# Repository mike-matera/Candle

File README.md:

Candle
======

This is the PCB designed for my candle controller. It's done using Eagle light.

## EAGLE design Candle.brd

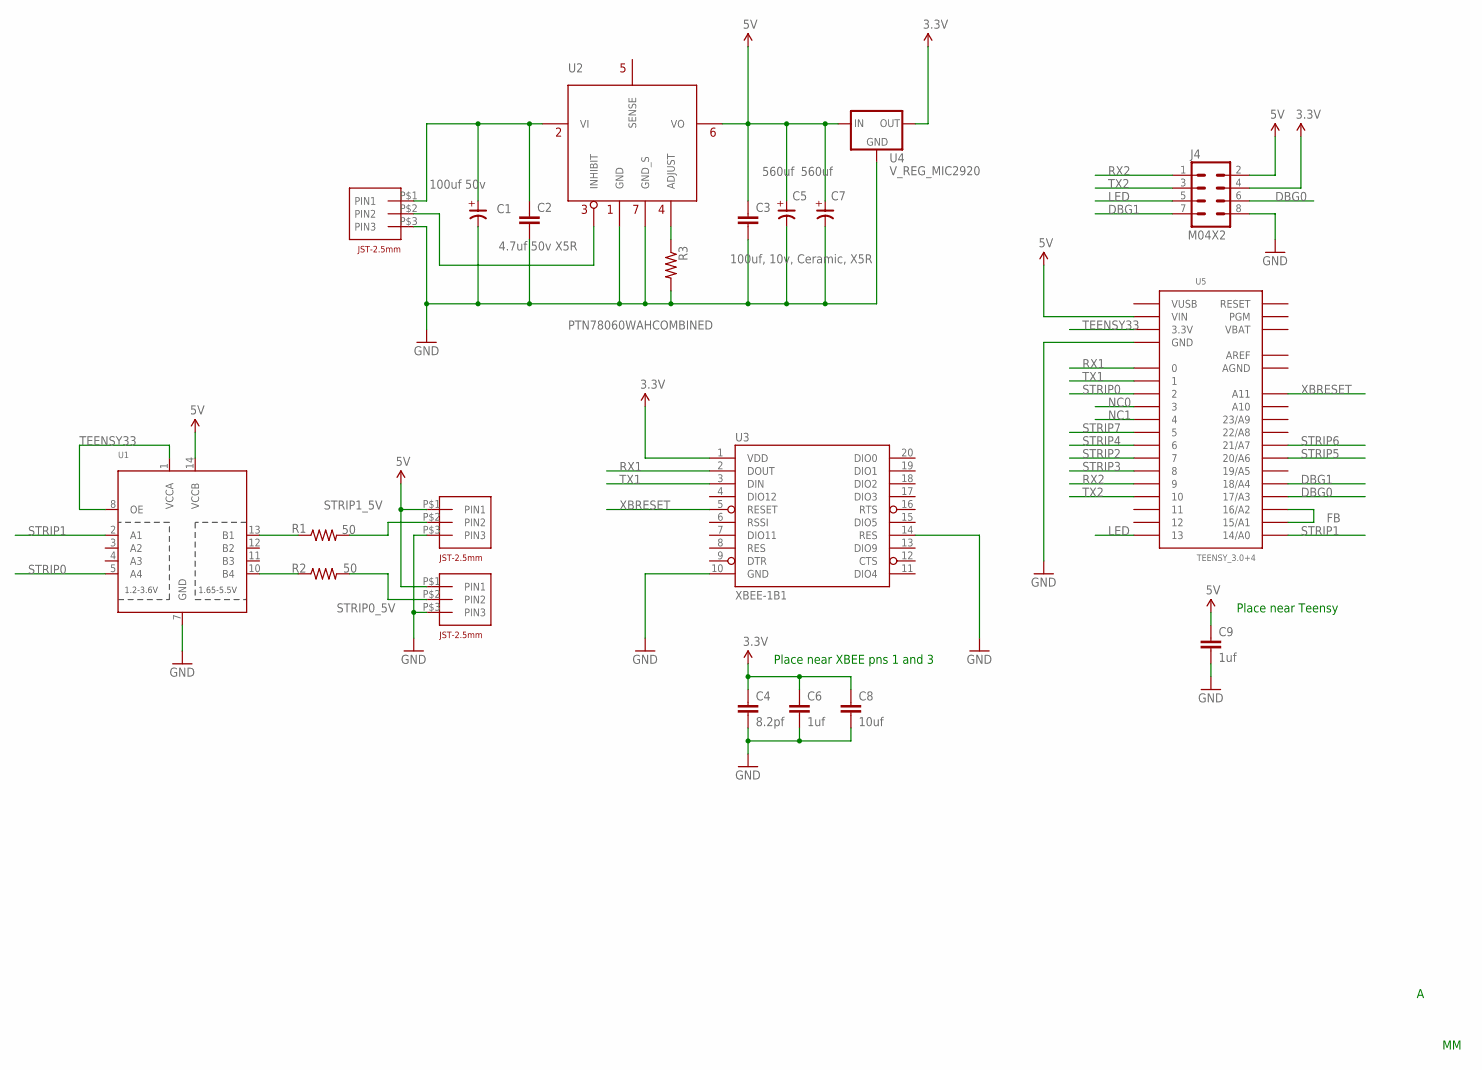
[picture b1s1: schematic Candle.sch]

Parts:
C1: 100uf 50v; SV-G
C2: 4.7uf 50v X5R; C3225
C3: 100uf, 10v, Ceramic, X5R; C3225
C4: 8.2pf; C3225
C5, C7: 560uf; SV-G
C6, C9: 1uf; C3225
C8: 10uf; C3225
J1, J2, J3: JST-XH-2.5MM-SIDE-3
J4: M04X2; 2X4
R1, R2: 50; R0805
R3: R-US_R0805; R0805
U1: TXB0104PWRSOIC14; SO14
U2: PTN78060WAHCOMBINED; COMBINED
U3: XBEE-1B1; XBEE-1
U4: V_REG_MIC2920; SOT223
U5: TEENSY_3.0+4

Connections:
3.3V: C4.1, C6.1, C8.1, J4.4, U3.1 (VDD), U4.3 (OUT)
5V: C3.1, C5.+, C7.+, C9.1, J2.P$1 (PIN1), J3.P$1 (PIN1), J4.2, U1.14 (VCCB), U2.VOUT (VO), U2.VOUT_S (VO), U4.1 (IN), U5.VIN
AGND: U5.AGND
AREF: U5.AREF
DBG0: J4.6, U5.17/A3
DBG1: J4.7, U5.18/A4
FB: U5.15/A1, U5.16/A2
GND: C1.-, C2.2, C3.2, C4.2, C5.-, C6.2, C7.-, C8.2, C9.2, J1.P$3 (PIN3), J2.P$3 (PIN3), J3.P$3 (PIN3), J4.8, R3.2, U1.7 (GND), U2.GND, U2.GND_S (GND), U2.S/GND (GND_S), U2.S/GND_S (GND_S), U3.10 (GND), U3.14 (RES), U4.2 (GND), U4.4 (GND), U5.GND, U5.GND1 (GND)
LED: J4.5, U5.13
unnamed: R1.1, U1.13 (B1)
unnamed: J1.P$2 (PIN2), U2.EN (INHIBIT)
unnamed: R2.1, U1.10 (B4)
NC0: U5.3
NC1: U5.4
RX1: U3.2 (DOUT), U5.0
RX2: J4.1, U5.9
STRIP0: U1.5 (A4), U5.2
STRIP0_5V: J3.P$2 (PIN2), R2.2
STRIP1: U1.2 (A1), U5.14/A0
STRIP1_5V: J2.P$2 (PIN2), R1.2
STRIP2: U5.7
STRIP3: U5.8
STRIP4: U5.6
STRIP5: U5.20/A6
STRIP6: U5.21/A7
STRIP7: U5.5
TEENSY33: U1.1 (VCCA), U1.8 (OE), U5.3.3V, U5.3.3V1 (3.3V)
TX1: U3.3 (DIN), U5.1
TX2: J4.3, U5.10
VADJ: R3.1, U2.ADJUST
VBAT: U5.VBAT
VIN: C1.+, C2.1, J1.P$1 (PIN1), U2.VIN (VI), U2.VIN_S (VI)
VUSB: U5.VUSB
XBRESET: U3.5 (RESET), U5.A11

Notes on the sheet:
Place near XBEE pns 1 and 3
Place near Teensy

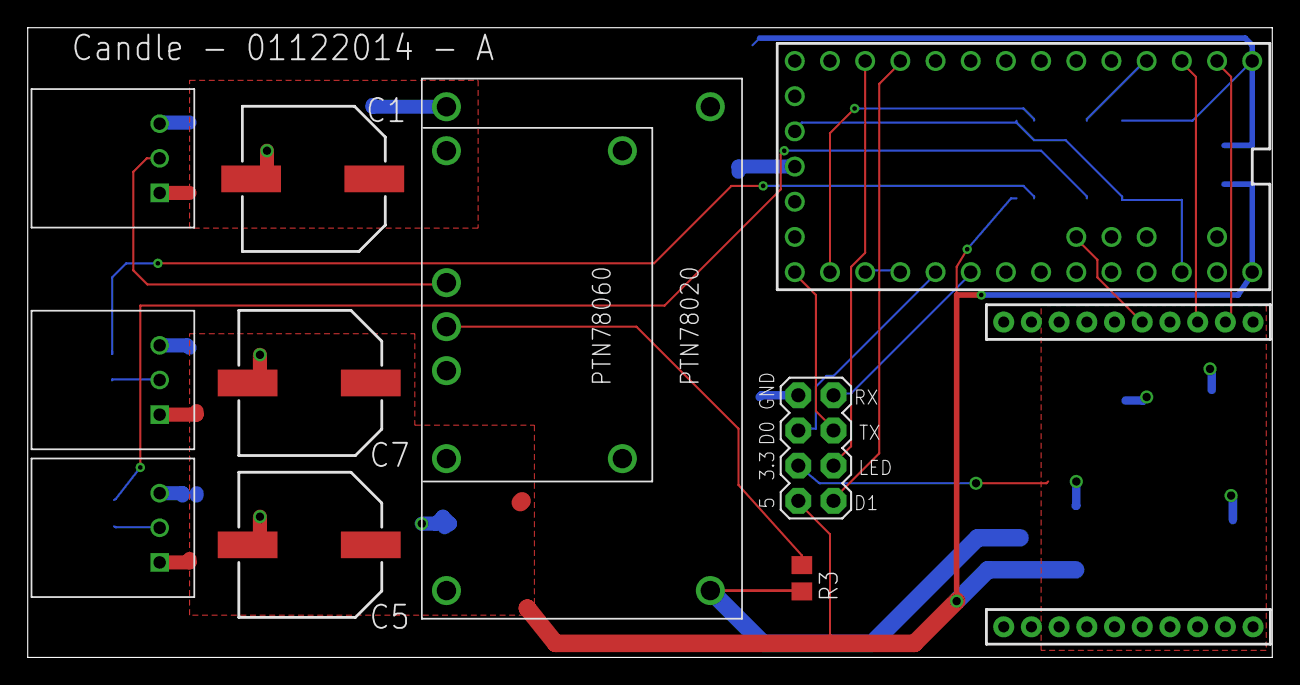
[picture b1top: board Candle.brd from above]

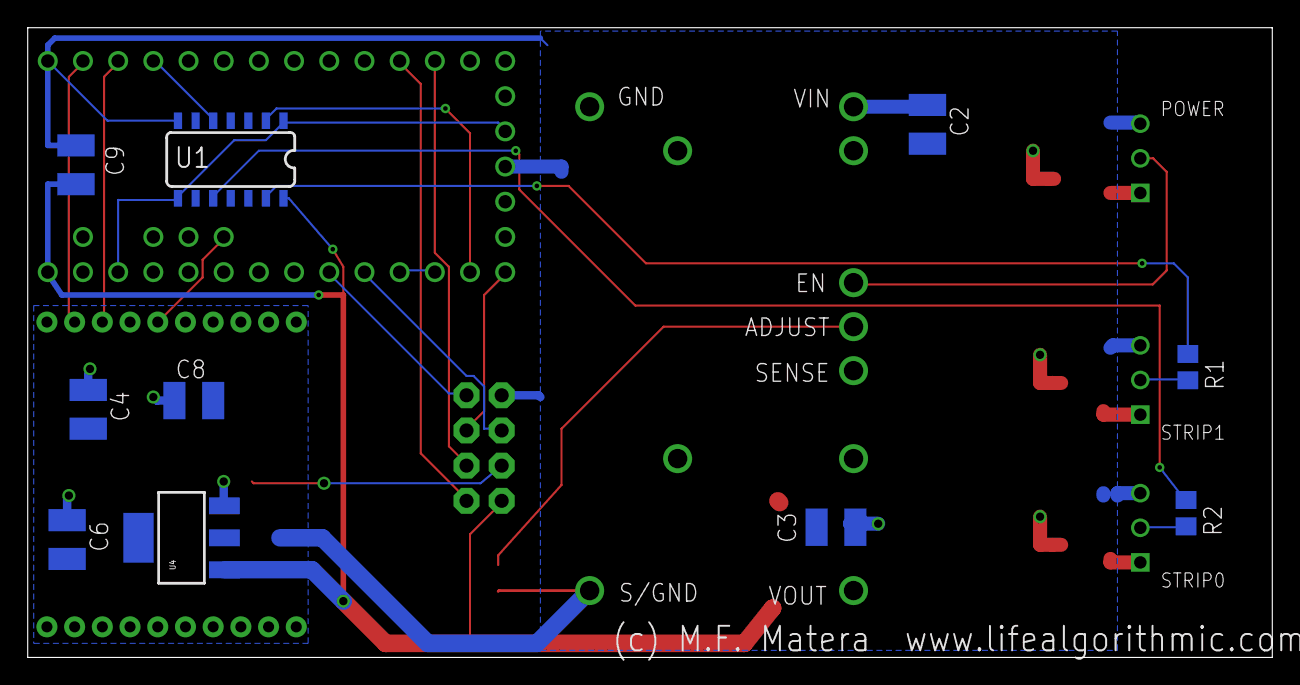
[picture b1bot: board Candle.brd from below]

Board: 2 copper layers, 89.8 x 45.5 mm, 21 parts (10 on the bottom side), 22 nets.

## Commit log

2014-01-25 First commit, board is built, footprints are verified.

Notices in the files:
parts and their libraries:
SparkFun-RF: Licensing: CC v3.0 Share-Alike You are welcome to use this library for commercial purposes.
